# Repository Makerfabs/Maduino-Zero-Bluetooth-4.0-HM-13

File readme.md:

# Maduino Zero Bluetooth 4.0 HM-13

```c++
/*
Version:		V1.0
Author:			Vincent
Create Date:	2021/5/8
Note:
	
*/
```

[toc]

# Makerfabs

[Makerfabs home page](https://www.makerfabs.com/)

[Makerfabs Wiki](https://makerfabs.com/wiki/index.php?title=Main_Page)

# Maduino Zero Bluetooth 4.0 HM-13

## Intruduce

Product Link ：[Maduino Zero Bluetooth 4.0 HM-13](https://www.makerfabs.com/maduino-zero-bluetooth-4.0-hm-13.html) 

Wiki Link :  [Maduino Zero Bluetooth 4.0 HM-13](https://www.makerfabs.com/wiki/index.php?title=Maduino_Zero_Bluetooth_4.0_HM-13) 

Maduino Zero HM-13 is an IoT (Internet of things) Solution based on the 32-bit Atmel's SAMD21 MCU and Bluetooth module HM-13. It integrated a micro Controller ATSAMD21G18, BLE module HM-13. The Maduino Zero HM-13 based on the Arduino, users can program it with Arduino IDE, which is very easy especially suit for the none-programmers. There are also guide for users to learn how to create the first IoT project with this board, with which the starters can learn the hardware and programming skill quickly. With this board, you will easy to add text, SMS, and data to your project. It is good for your smart home project or M2M and so on.

## Feature

- BAT Input Voltage: 3.4-4.2V
- ATSAMD21G18, 32-Bit ARM Cortex M0+
- Integrated Power Control System
- Support AT Command
- BLE and SPP Bluetooth Profile Support
- Support USB Power Charge
- Support Micro SD Card
- Interface: I2C/SPI/UART/18*GPIO*
- *Arduino Compatible*
- *Working Temperature: -40 – 85℃*
- *Size: 40mm*55mm

### Front:

### Back:

## Compiler Options
**If you have any questions，such as how to install the development board, how to download the code, how to install the library. Please refer to :[Makerfabs_FAQ](https://github.com/Makerfabs/Makerfabs_FAQ)**

- Select "Arduino Zero(Native USB port)"

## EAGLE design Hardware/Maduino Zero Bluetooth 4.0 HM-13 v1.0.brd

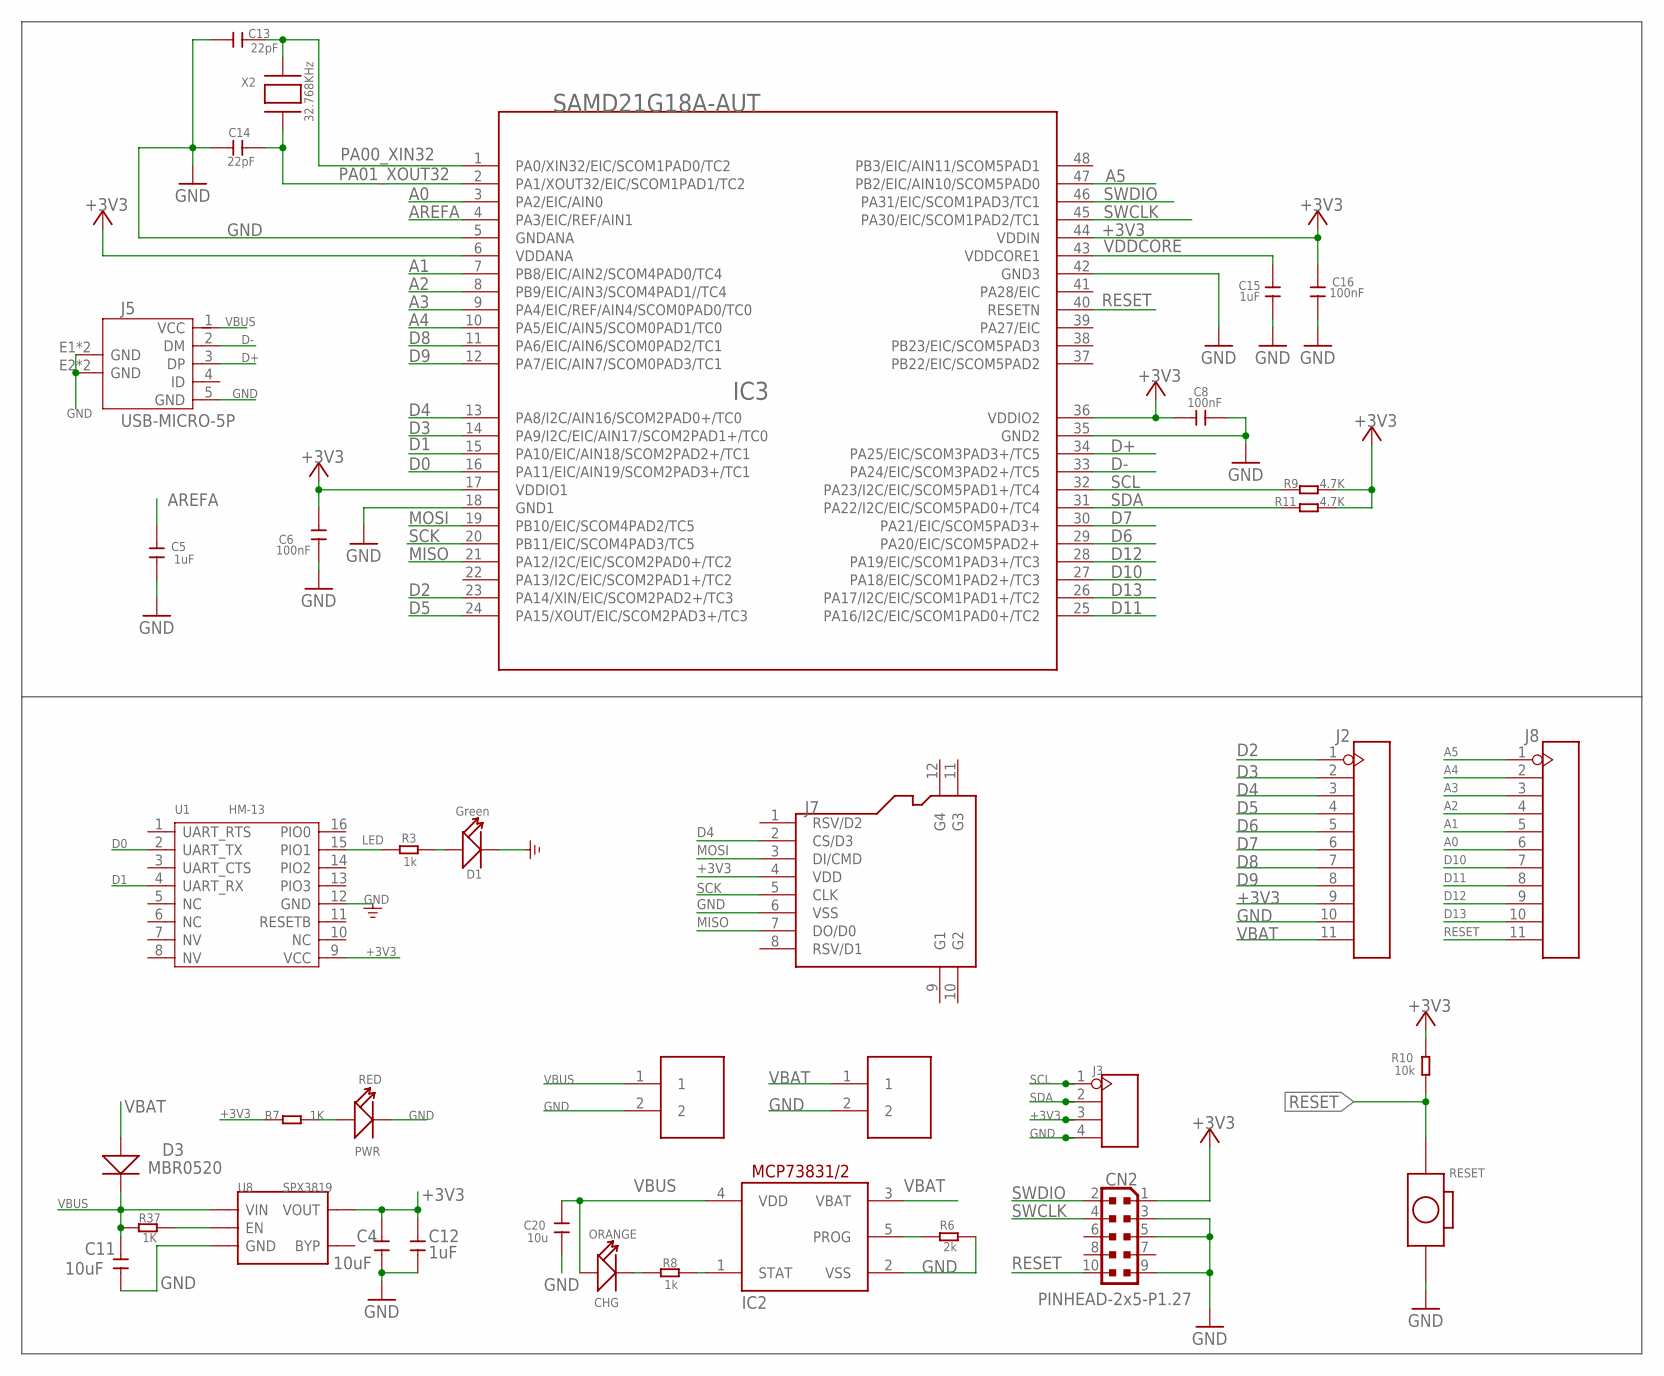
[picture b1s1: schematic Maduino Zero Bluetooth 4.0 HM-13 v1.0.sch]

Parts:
C4, C11: 10uF; 0603
C5, C12, C15: 1uF; 0603
C6, C8, C16: 100nF; 0603
C13, C14: 22pF; 0603
C20: 10u; 0603
CHG: ORANGE; D0603
CN2: PINHEAD-2x5-P1.27; PINHEAD_2X05_127
D1: Green; LED-0603
D3: MBR0520; SOD123
IC2: MCP73831/OT; SOT23-5L
IC3: SAMD21G18A-AUT; TQFP48-7X7
J1, J6: PH2.0-2P-90-DIP
J2, J8: HEADER-11P-2.54; 11P-2.54
J3: HEADER-4P-60/35MILROUND; 4P-65/35ROUND
J5: USB-MICRO-5P; MICRO-USB-5P
J7: HOLDER-MICROSD-8P; 8P-SMD
PWR: RED; LED-0603
R3, R8: 1k; R0603
R6: 2k; R0603
R7, R37: 1K; R0603
R9, R11: 4.7K; R0603
R10: 10k; R0603
RESET: BOTTON-2P-90D; 2P-7.62X3.56-90D
U1: HM-13; 16P-18.5X13.5X0.8
U8: SPX3819; SOT23-5
X2: 32.768KHz; XTAL3215

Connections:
+3V3: C4.2, C6.2, C8.1, C12.2, C16.1, CN2.1, IC3.6 (VDDANA), IC3.17 (VDDIO1), IC3.36 (VDDIO2), IC3.44 (VDDIN), J2.9, J3.3, J7.4 (VDD), R7.1, R9.2, R10.2, R11.2, U1.9 (VCC), U8.5 (VOUT)
A0: IC3.3 (PA2/EIC/AIN0), J8.6
A1: IC3.7 (PB8/EIC/AIN2/SCOM4PAD0/TC4), J8.5
A2: IC3.8 (PB9/EIC/AIN3/SCOM4PAD1//TC4), J8.4
A3: IC3.9 (PA4/EIC/REF/AIN4/SCOM0PAD0/TC0), J8.3
A4: IC3.10 (PA5/EIC/AIN5/SCOM0PAD1/TC0), J8.2
A5: IC3.47 (PB2/EIC/AIN10/SCOM5PAD0), J8.1
AREFA: C5.1, IC3.4 (PA3/EIC/REF/AIN1)
D0: IC3.16 (PA11/EIC/AIN19/SCOM2PAD3+/TC1), U1.2 (UART_TX)
D1: IC3.15 (PA10/EIC/AIN18/SCOM2PAD2+/TC1), U1.4 (UART_RX)
D2: IC3.23 (PA14/XIN/EIC/SCOM2PAD2+/TC3), J2.1
D3: IC3.14 (PA9/I2C/EIC/AIN17/SCOM2PAD1+/TC0), J2.2
D4: IC3.13 (PA8/I2C/AIN16/SCOM2PAD0+/TC0), J2.3, J7.2 (CS/D3)
D5: IC3.24 (PA15/XOUT/EIC/SCOM2PAD3+/TC3), J2.4
D6: IC3.29 (PA20/EIC/SCOM5PAD2+), J2.5
D7: IC3.30 (PA21/EIC/SCOM5PAD3+), J2.6
D8: IC3.11 (PA6/EIC/AIN6/SCOM0PAD2/TC1), J2.7
D9: IC3.12 (PA7/EIC/AIN7/SCOM0PAD3/TC1), J2.8
D10: IC3.27 (PA18/EIC/SCOM1PAD2+/TC3), J8.7
D11: IC3.25 (PA16/I2C/EIC/SCOM1PAD0+/TC2), J8.8
D12: IC3.28 (PA19/EIC/SCOM1PAD3+/TC3), J8.9
D13: IC3.26 (PA17/I2C/EIC/SCOM1PAD1+/TC2), J8.10
D+: IC3.34 (PA25/EIC/SCOM3PAD3+/TC5), J5.3 (DP)
D-: IC3.33 (PA24/EIC/SCOM3PAD2+/TC5), J5.2 (DM)
GND: C4.1, C5.2, C6.1, C8.2, C11.1, C12.1, C13.2, C14.2, C15.2, C16.2, C20.1, CN2.3, CN2.5, CN2.9, D1.-, IC2.2 (VSS), IC3.5 (GNDANA), IC3.18 (GND1), IC3.35 (GND2), IC3.42 (GND3), J1.2, J2.10, J3.4, J5.5 (GND), J5.E1 (GND), J5.E2 (GND), J5.P1 (GND), J5.P2 (GND), J6.2, J7.6 (VSS), PWR.-, R6.2, RESET.P$2 (2), U1.12 (GND), U8.2 (GND)
LED: R3.1, U1.15 (PIO1)
MISO: IC3.21 (PA12/I2C/EIC/SCOM2PAD0+/TC2), J7.7 (DO/D0)
MOSI: IC3.19 (PB10/EIC/SCOM4PAD2/TC5), J7.3 (DI/CMD)
unnamed: PWR.+, R7.2
unnamed: D1.+, R3.2
unnamed: R37.2, U8.3 (EN)
unnamed: CHG.-, R8.1
unnamed: IC2.1 (STAT), R8.2
unnamed: IC2.5 (PROG), R6.1
PA00_XIN32: C13.1, IC3.1 (PA0/XIN32/EIC/SCOM1PAD0/TC2), X2.P$2
PA01_XOUT32: C14.1, IC3.2 (PA1/XOUT32/EIC/SCOM1PAD1/TC2), X2.P$1
RESET: CN2.10, IC3.40 (RESETN), J8.11, R10.1, RESET.P$1 (1)
SCK: IC3.20 (PB11/EIC/SCOM4PAD3/TC5), J7.5 (CLK)
SCL: IC3.32 (PA23/I2C/EIC/SCOM5PAD1+/TC4), J3.1, R9.1
SDA: IC3.31 (PA22/I2C/EIC/SCOM5PAD0+/TC4), J3.2, R11.1
SWCLK: CN2.4, IC3.45 (PA30/EIC/SCOM1PAD2/TC1)
SWDIO: CN2.2, IC3.46 (PA31/EIC/SCOM1PAD3/TC1)
VBAT: D3.+, IC2.3 (VBAT), J2.11, J6.1
VBUS: C11.2, C20.2, CHG.+, D3.-, IC2.4 (VDD), J1.1, J5.1 (VCC), R37.1, U8.1 (VIN)
VDDCORE: C15.1, IC3.43 (VDDCORE1)

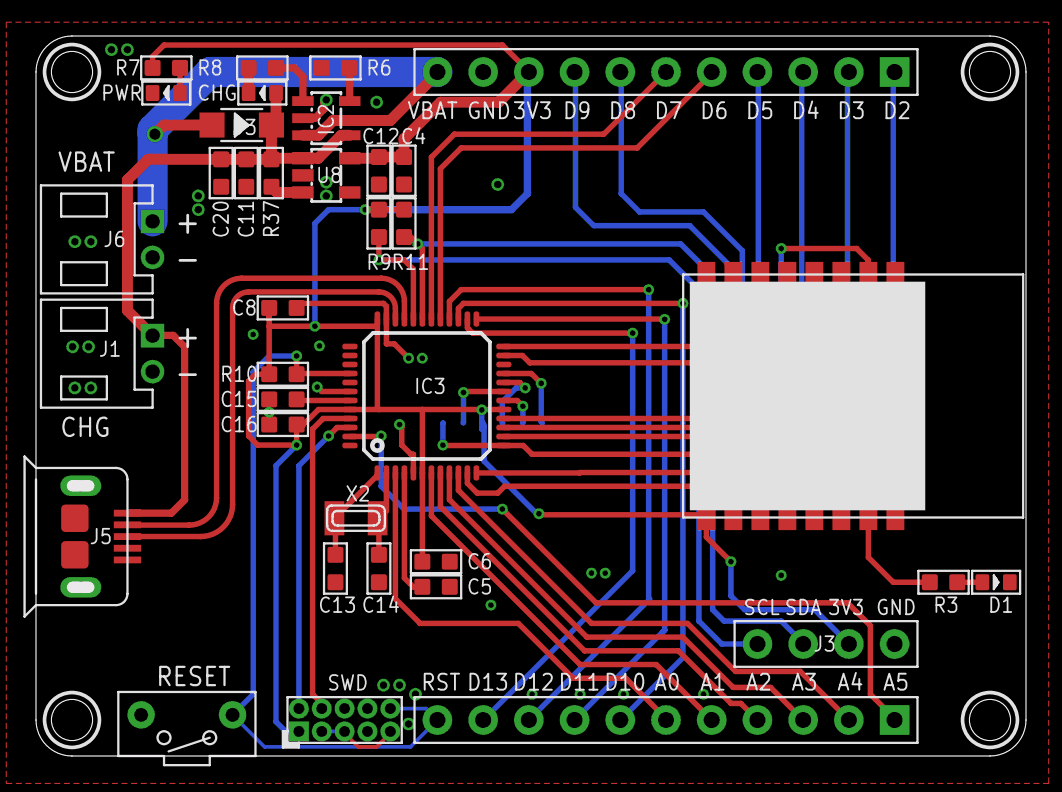
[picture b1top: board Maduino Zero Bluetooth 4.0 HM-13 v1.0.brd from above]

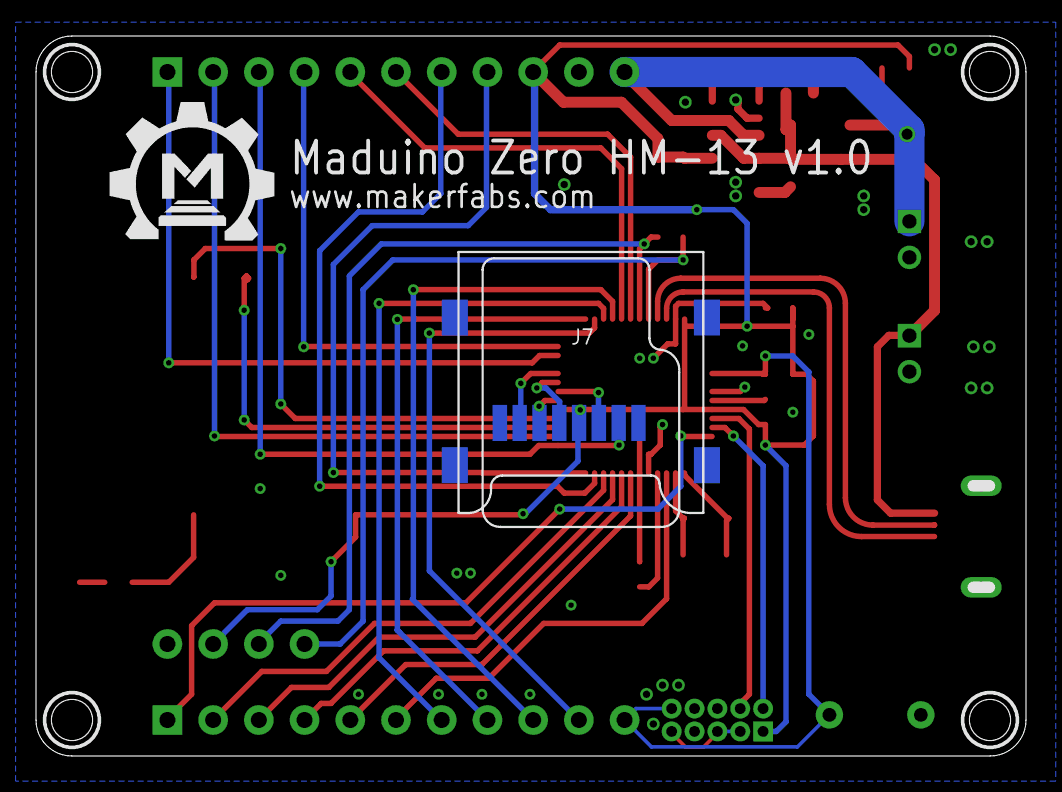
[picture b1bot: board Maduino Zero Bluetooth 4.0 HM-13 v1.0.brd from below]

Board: 2 copper layers, 54.4 x 39.4 mm, 38 parts (2 on the bottom side), 45 nets.

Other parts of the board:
U$1: MAKERFABS_0.3

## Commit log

2021-02-19 create
2021-05-08 Add readme
